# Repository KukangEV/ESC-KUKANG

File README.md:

## Why are We Building Electronic Speed Controller?

Creating an open source ESC can provide a significant contribution to the development of electric vehicles and EV technology in general. By making this technology openly available, developers and EV enthusiasts in Indonesia and around the world can easily access and modify the ESC.

In addition, by accelerating the development of EV, we can reduce our dependence on dwindling fossil fuels and produce fewer carbon emissions that harm the environment. Through open source ESC, we can encourage the development of more efficient and environmentally friendly technologies for future vehicles.

Moreover, this project can inspire young Indonesians to become more active in the automotive and EV technology industry. With an open source platform, we can develop creativity and innovative ideas that can help produce better technology and advance the automotive industry in Indonesia and around the world. Thus, this project will have a long-term positive impact on society and the environment.

## What is the ESC-KUKANG?

ESC (Electronic Speed Controller) is an important component in electric vehicles, including for the purposes of the Shell Eco-marathon. The ESC functions to control the current and voltage supplied to the DC motor in electric vehicles. The ESC usually uses a MOSFET as a switch which is regulated by a control circuit, and uses PWM (Pulse Width Modulation) to control the speed of the motor.

In the context of the Shell Eco-marathon, the ESC used must be designed in such a way that it is efficient in energy use, lightweight, and can produce power output as needed. This is very important because the vehicle must have enough endurance to cover the required distance with minimal battery usage.

To achieve this goal, several things that need to be considered in the ESC design for Shell Eco-marathon are the selection of components that are efficient and can work at high frequencies (around 16 kHz), the use of MOSFETs with low Rds-on values, the use of appropriate capacitors at input and output regulators to minimize noise and ripple, and the use of a PCB (Printed Circuit Board) with a good layout to minimize noise and EMI (Electromagnetic Interference). In addition, the ESC design must also consider safety factors and protection against overcurrent, overvoltage and overheating.

## How does it work?

ESC (Electronic Speed Controller) is an electronic circuit that functions to control the speed of an electric motor. When given a control signal from the remote or other controller, the ESC will convert the signal into a control signal to speed up or slow down the motor rotation.

ESC works by adjusting the amount of energy supplied to the motor. The ESC regulates the electric current that is supplied to the motor via a MOSFET or other power transistor. When the ESC receives a stronger control signal, the MOSFET opens wide and allows a greater amperage to flow to the motor, causing the motor to spin faster. Conversely, when the ESC receives a weaker control signal, the MOSFET will close more and limit the amperage flowing to the motor, causing the motor to rotate more slowly.

The ESC is also equipped with security protections such as protection from overcurrent, overheat and low voltage which will turn off the motor if there is a problem with the system.

## Installation
coming soon
## Contributors

## License

This project is licensed under the Apache 2 License - see the [LICENSE](LICENSE) file for details.

## Version

See `library.json` (PlatformIO) or `library.properties` (Arduino).

v0.0.1

[KUKANG-EV]: <https://kukang-ev.tech/>

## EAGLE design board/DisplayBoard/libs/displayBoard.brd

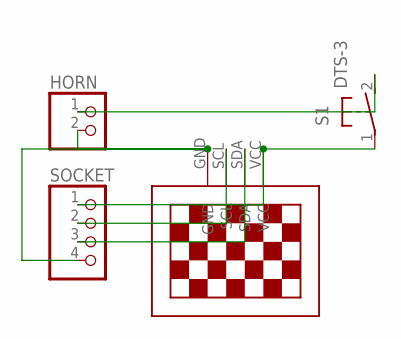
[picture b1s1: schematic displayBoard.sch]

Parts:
HORN: PINHD-1X2; 1X02
S1: DTS-3
SOCKET: PINHD-1X4; 1X04
U$1: 13"OLED13"OLED; 1.3"OLED

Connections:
unnamed: HORN.1, S1.2
unnamed: S1.1, SOCKET.1, U$1.VCC
unnamed: HORN.2, SOCKET.4, U$1.GND
unnamed: SOCKET.2, U$1.SCL
unnamed: SOCKET.3, U$1.SDA

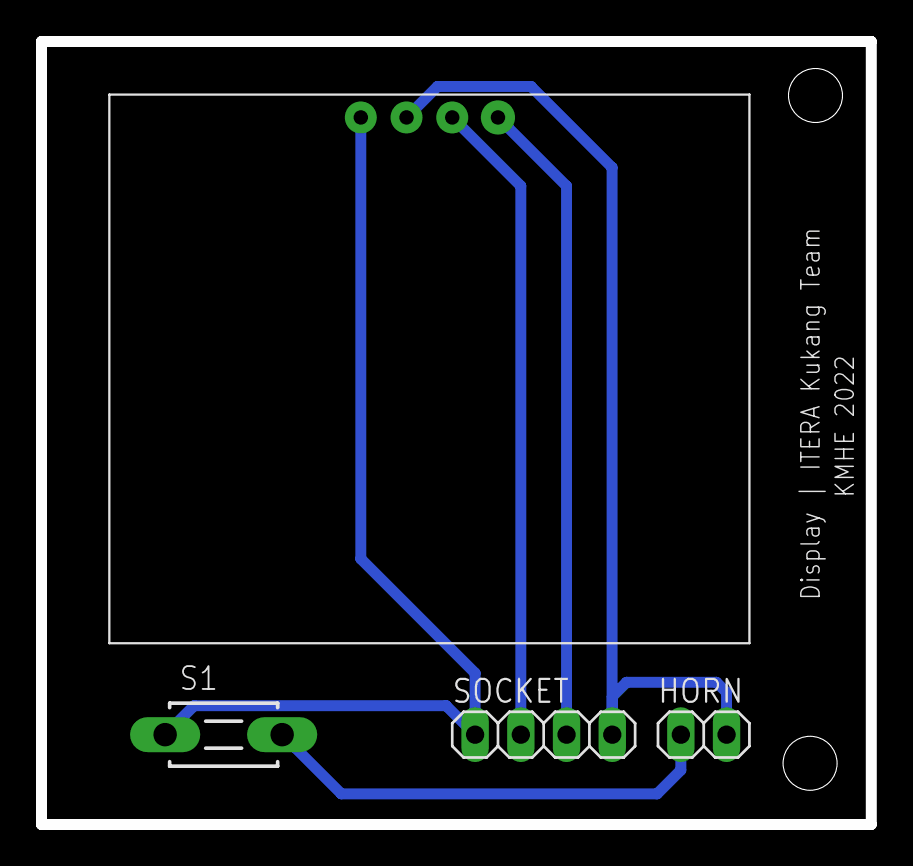
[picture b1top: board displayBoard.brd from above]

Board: 2 copper layers, 46.1 x 43.5 mm, 4 parts (0 on the bottom side), 5 nets.

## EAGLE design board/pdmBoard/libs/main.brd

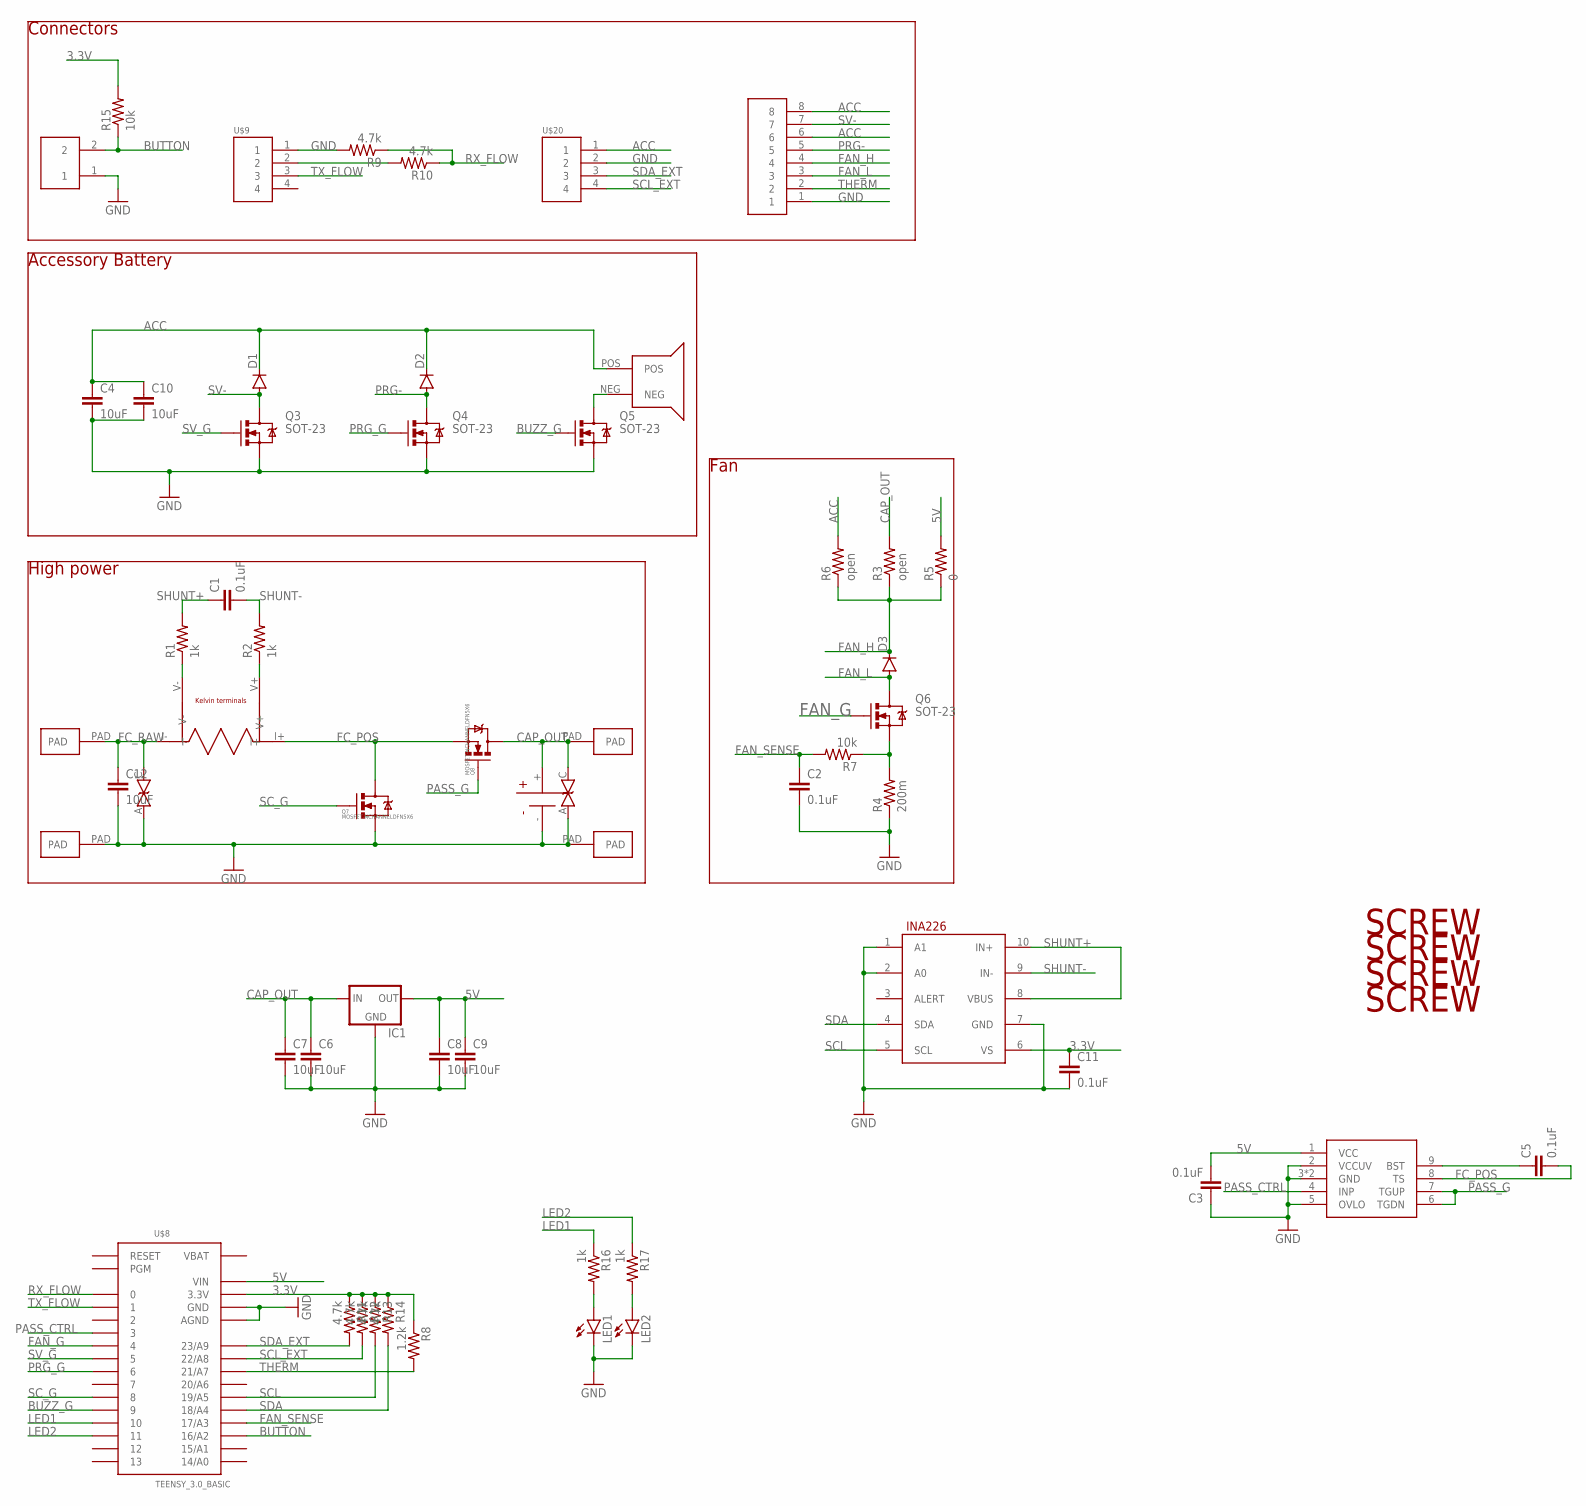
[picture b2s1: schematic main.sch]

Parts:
C1, C2, C3, C5, C11: 0.1uF; 0603-CAP
C4, C6, C7, C8, C9, C10, C12: 10uF; 1206
D1, D2, D3: DIODESOD123; SOD-123
IC1: V_REG_78XXV78W; V78W
LED1, LED2: LED1206; LED-1206
Q3, Q4, Q5, Q6: SOT-23; SOT23-3
Q7, Q8: MOSFET-NCHANNELDFN5X6; DFN5X6
R1, R2, R16, R17: 1k; 0603-RES
R3, R6: open; 0603-RES
R4: 200m; 0603-RES
R5: 0; 0603-RES
R7, R15: 10k; 0603-RES
R8: 1.2k; 0603-RES
R9, R10, R11, R12, R13, R14: 4.7k; 0603-RES
U$1: SHUNT_KELVIN; 2512_KELVIN
U$2: INA226; PSOP-10
U$3, U$4, U$10, U$11: PAD
U$5: HEADER8; 8PINVALULOK
U$6: LTC7001; PSOP-10-EP
U$7: BUZZER12MM; BUZZER_12MM
U$8: TEENSY_3.0_BASIC
U$9, U$20: HEADER4VALULOK; 4PINVALULOK
U$12: CAP-AL_ELECTROLYTIC; CAP-RADIAL
U$13: HEADER2; 2PINVALULOK
U$14, U$15, U$18, U$19: SCREW; M3HOLE
U$16, U$17: TVS_BIDO-214AB; DO-214AB

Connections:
3.3V: C11.1, R8.1, R11.1, R12.1, R13.1, R14.1, R15.2, U$2.6 (VS), U$8.3.3V, U$8.3.3V1 (3.3V)
5V: C3.2, C8.1, C9.1, IC1.OUT, R5.2, U$6.1 (VCC), U$8.VIN
ACC: C4.1, C10.1, D1.C, D2.C, R6.2, U$5.6, U$5.8, U$7.POS, U$20.1
BUTTON: R15.1, U$8.16/A2, U$13.2
BUZZ_G: Q5.1 (G), U$8.9
CAP_OUT: C6.1, C7.1, IC1.IN, Q8.PAD (D), R3.2, U$10.PAD, U$12.+ (V+), U$17.C (2)
FAN_G: Q6.1 (G), U$8.4
FAN_H: D3.C, R3.1, R5.1, R6.1, U$5.4
FAN_L: D3.A, Q6.3 (D), U$5.3
FAN_SENSE: C2.1, R7.2, U$8.17/A3
FC_POS: C5.2, Q7.PAD (D), Q8.1 (S), Q8.2 (S), Q8.3 (S), U$1.I+, U$6.8 (TS)
FC_RAW: C12.1, U$1.I-, U$3.PAD, U$16.C (2)
GND: C2.2, C3.1, C4.2, C6.2, C7.2, C8.2, C9.2, C10.2, C11.2, C12.2, IC1.GND, LED1.C, LED2.C, Q3.2 (S), Q4.2 (S), Q5.2 (S), Q7.1 (S), Q7.2 (S), Q7.3 (S), R4.1, R9.2, U$2.1 (A1), U$2.2 (A0), U$2.7 (GND), U$4.PAD, U$5.1, U$6.2 (VCCUV), U$6.3 (GND), U$6.5 (OVLO), U$6.PAD (GND), U$8.AGND, U$8.GND, U$8.GND1 (GND), U$9.1, U$11.PAD, U$12.- (V-), U$13.1, U$16.A (1), U$17.A (1), U$20.2
LED1: R16.1, U$8.10
LED2: R17.1, U$8.11
unnamed: C5.1, U$6.9 (BST)
unnamed: LED1.A, R16.2
unnamed: Q5.3 (D), U$7.NEG
unnamed: R1.1, U$1.V-
unnamed: R2.1, U$1.V+
unnamed: Q6.2 (S), R4.2, R7.1
unnamed: R10.2, U$9.2
unnamed: LED2.A, R17.2
PASS_CTRL: U$6.4 (INP), U$8.3
PASS_G: Q8.4 (G), U$6.6 (TGDN), U$6.7 (TGUP)
PRG-: D2.A, Q4.3 (D), U$5.5
PRG_G: Q4.1 (G), U$8.6
RX_FLOW: R9.1, R10.1, U$8.0
SCL: R13.2, U$2.5 (SCL), U$8.19/A5
SCL_EXT: R12.2, U$8.22/A8, U$20.4
SC_G: Q7.4 (G), U$8.8
SDA: R14.2, U$2.4 (SDA), U$8.18/A4
SDA_EXT: R11.2, U$8.23/A9, U$20.3
SHUNT+: C1.1, R1.2, U$2.8 (VBUS), U$2.10 (IN+)
SHUNT-: C1.2, R2.2, U$2.9 (IN-)
SV-: D1.A, Q3.3 (D), U$5.7
SV_G: Q3.1 (G), U$8.5
THERM: R8.2, U$5.2, U$8.21/A7
TX_FLOW: U$8.1, U$9.3
VBAT: U$8.VBAT

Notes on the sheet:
Accessory Battery
High power
Fan
Connectors

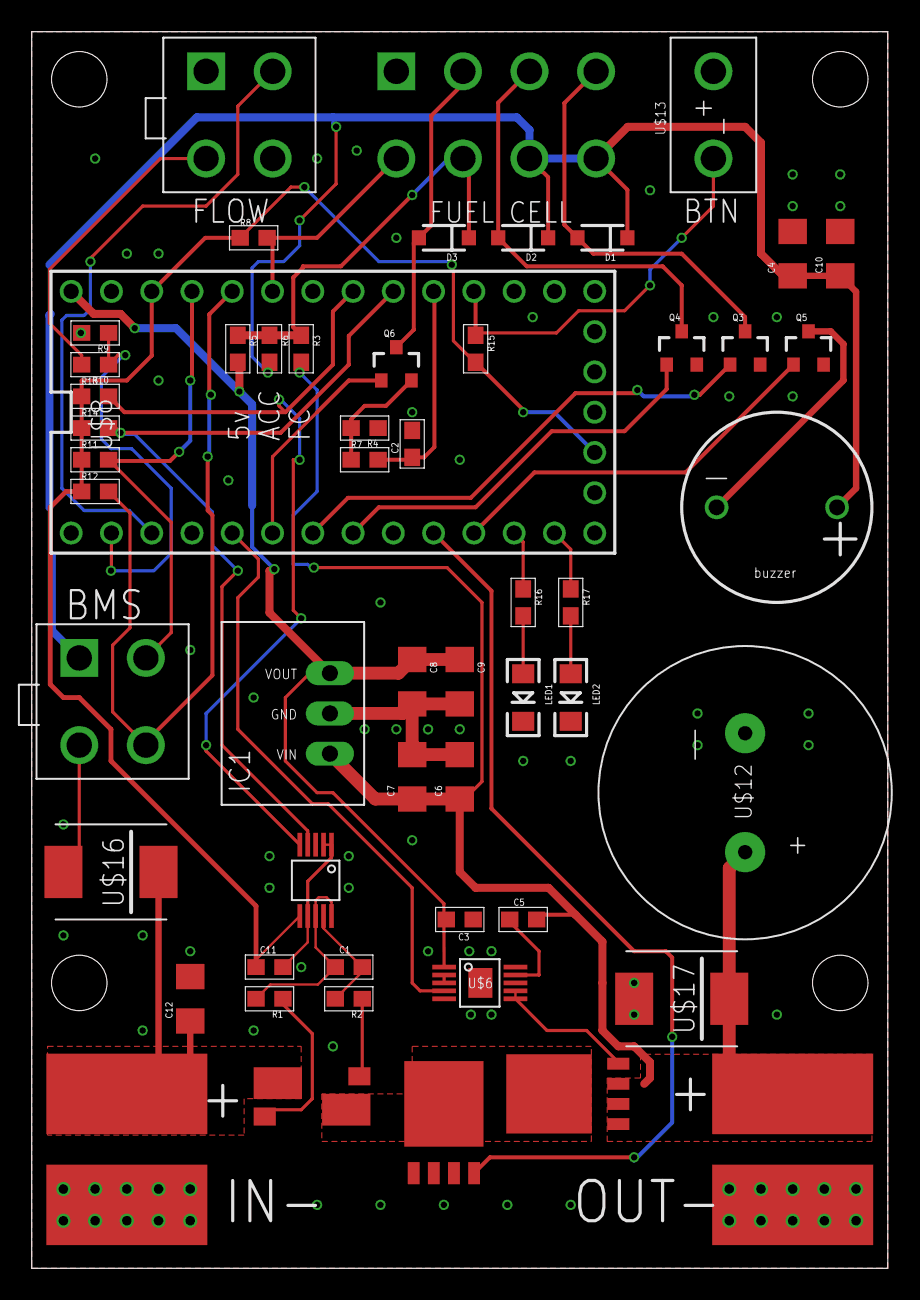
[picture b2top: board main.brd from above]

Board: 2 copper layers, 54.0 x 78.0 mm, 61 parts (0 on the bottom side), 39 nets.

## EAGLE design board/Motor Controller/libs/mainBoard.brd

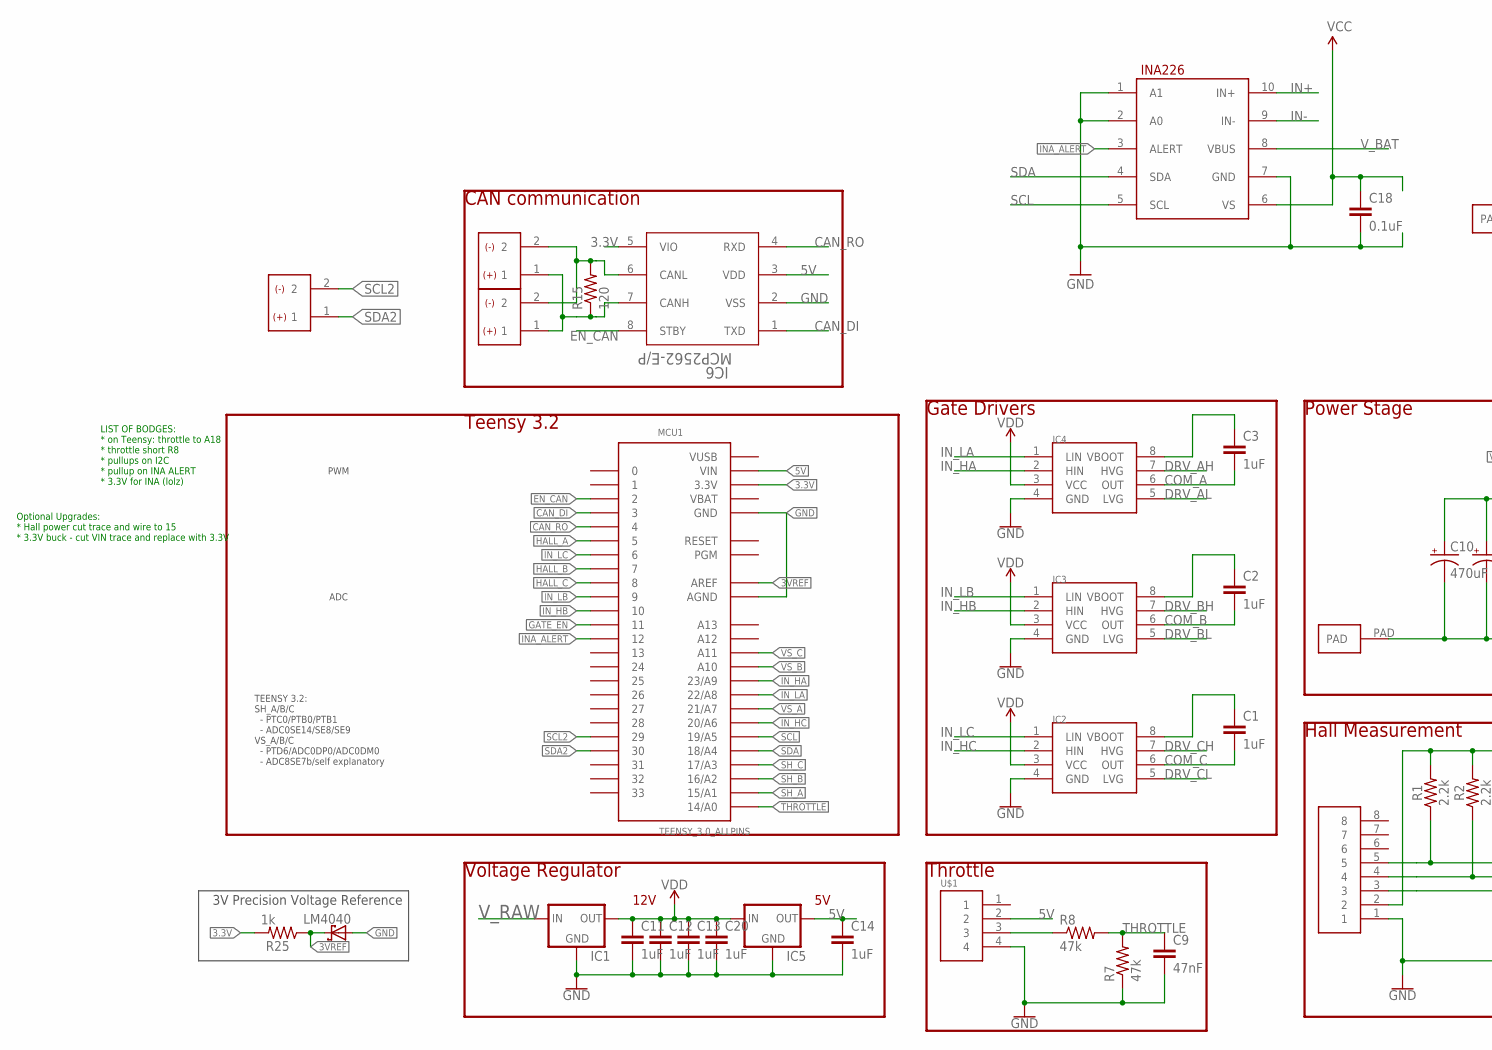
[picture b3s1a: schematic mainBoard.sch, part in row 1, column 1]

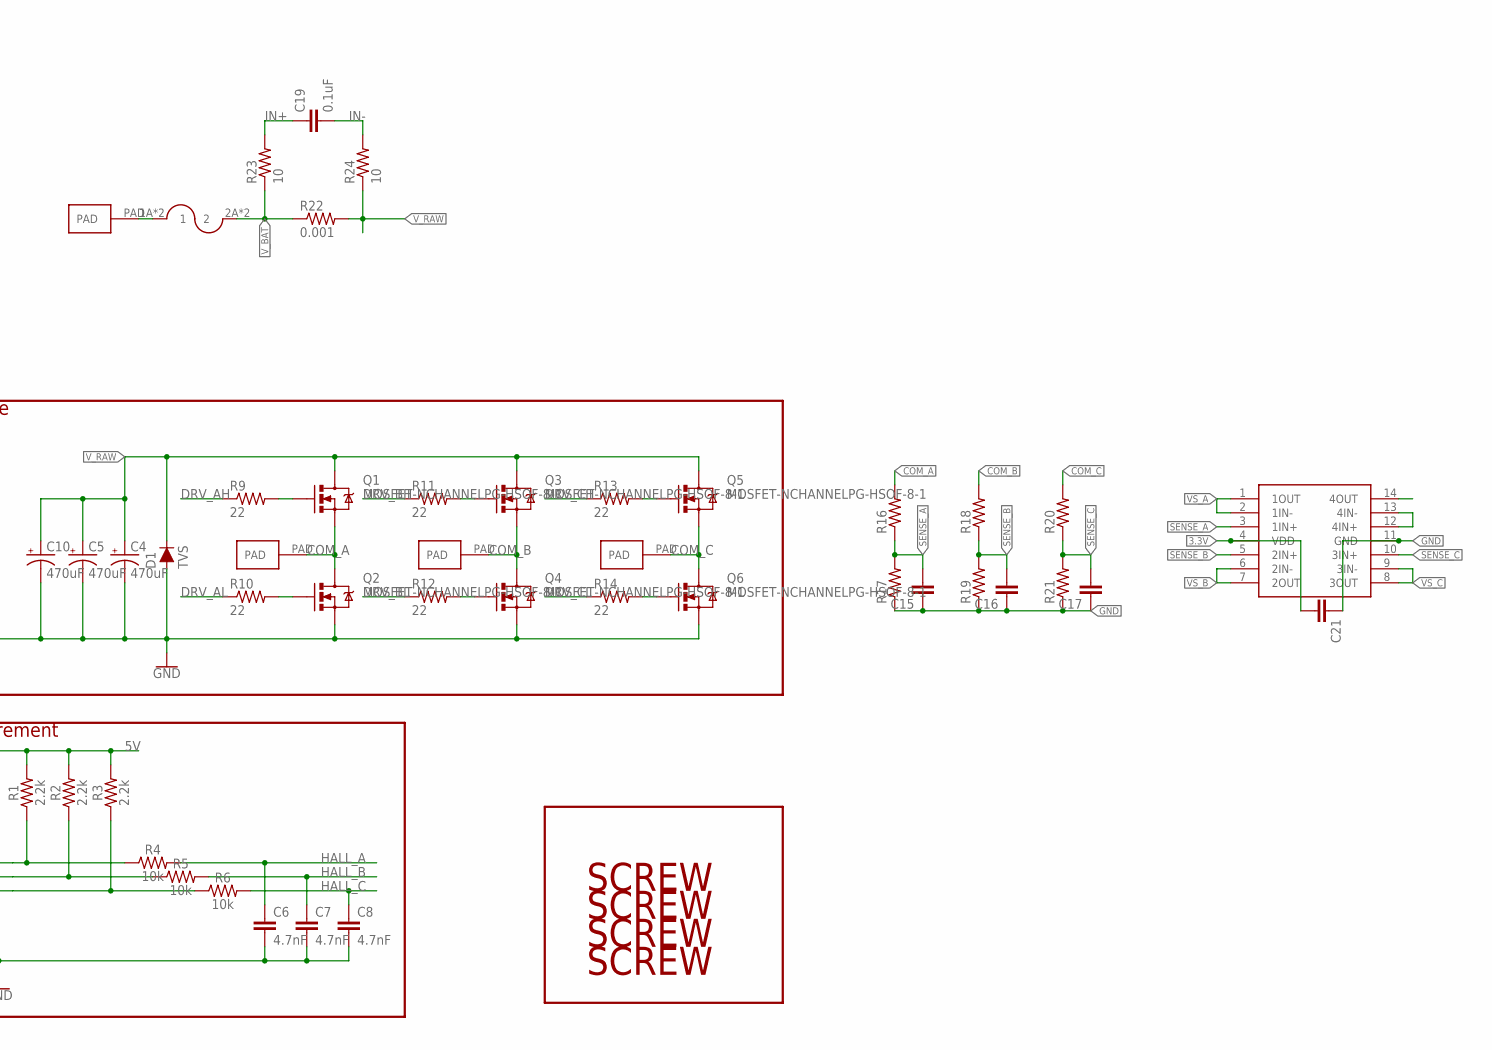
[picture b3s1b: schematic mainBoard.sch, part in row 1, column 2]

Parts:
C1, C2, C3, C11, C12, C13, C14, C20: 1uF; CAP-PTH-SMALL-KIT
C4, C5, C10: 470uF; CPOL-RADIAL-5MM-10MM
C6, C7, C8: 4.7nF; 0603-CAP
C9: 47nF; 0603-CAP
C15, C16, C17, C21: CAP0603-CAP; 0603-CAP
C18, C19: 0.1uF; 0603-CAP
CAN1, CAN2: HEADER2; 2PINVALULOK
D1: TVS; DIODE-1N4001
I2C: HEADER2; 2PINVALULOK
IC1: V_REG_78XX; V78W_BACKWARDS
IC2, IC3, IC4: L6387EDIP8; DIP762W53P254L1092H508Q8B
IC5: V_REG_78XXV78W; V78W
IC6: MCP2562-E/P; PDIP8_300MC
IC7: INA226; PSOP-10
J3: FUSE; AUTO_FUSE
MCU1: TEENSY_3.0_ALLPINS
Q1, Q2, Q3, Q4, Q5, Q6: MOSFET-NCHANNELPG-HSOF-8-1; PG-HSOF-8-1
R1, R2, R3: 2.2k; 0603-RES
R4, R5, R6: 10k; 0603-RES
R7, R8: 47k; 0603-RES
R9, R10, R11, R12, R13, R14: 22; 0603-RES
R15: 120; 0603-RES
R16, R17, R18, R19, R20, R21: RESISTOR0603-RES; 0603-RES
R22: 0.001; R2512
R23, R24: 10; 0603-RES
R25: 1k; 0603-RES
U$1: HEADER4VALULOK; 4PINVALULOK
U$2: OPAMP_QUAD; TSSOP-14
U$4, U$5, U$6, U$7, U$8: PAD
U$10, U$11, U$12, U$13: SCREW; M3HOLE
U$14: HEADER8; 8PINVALULOK
U$15: LM4040; SOT23-3

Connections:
3.3V: C21.2, IC6.5 (VIO), MCU1.3.3V, MCU1.3.3V1 (3.3V), MCU1.3.3V2 (3.3V), R25.2, U$2.4 (VDD)
3VREF: MCU1.AREF, R25.1, U$15.1 (C)
5V: C14.1, IC5.OUT, IC6.3 (VDD), MCU1.VIN, R1.2, R2.2, R3.2, U$1.2, U$14.2
CANH: CAN1.1, CAN2.1, IC6.7 (CANH), R15.1
CANL: CAN1.2, CAN2.2, IC6.6 (CANL), R15.2
CAN_DI: IC6.1 (TXD), MCU1.3
CAN_RO: IC6.4 (RXD), MCU1.4
COM_A: C3.2, IC4.6 (OUT), Q1.S, Q2.D, R16.2, U$6.PAD
COM_B: C2.2, IC3.6 (OUT), Q3.S, Q4.D, R18.2, U$7.PAD
COM_C: C1.2, IC2.6 (OUT), Q5.S, Q6.D, R20.2, U$8.PAD
DRV_AH: IC4.7 (HVG), R9.1
DRV_AL: IC4.5 (LVG), R10.1
DRV_BH: IC3.7 (HVG), R11.1
DRV_BL: IC3.5 (LVG), R12.1
DRV_CH: IC2.7 (HVG), R13.1
DRV_CL: IC2.5 (LVG), R14.1
EN_CAN: IC6.8 (STBY), MCU1.2
GATE_EN: MCU1.11
GND: C4.-, C5.-, C6.2, C7.2, C8.2, C9.2, C10.-, C11.2, C12.2, C13.2, C14.2, C15.1, C16.1, C17.1, C18.2, C20.2, C21.1, D1.A, IC1.GND, IC2.4 (GND), IC3.4 (GND), IC4.4 (GND), IC5.GND, IC6.2 (VSS), IC7.1 (A1), IC7.2 (A0), IC7.7 (GND), MCU1.AGND, MCU1.GND, MCU1.GND1 (GND), MCU1.GND2 (GND), Q2.S, Q4.S, Q6.S, R7.1, R17.1, R19.1, R21.1, U$1.4, U$2.11 (GND), U$5.PAD, U$14.1, U$15.2 (A)
HALL_A: C6.1, MCU1.5, R4.2
HALL_B: C7.1, MCU1.7, R5.2
HALL_C: C8.1, MCU1.8, R6.2
IN+: C19.1, IC7.10 (IN+), R23.2
IN-: C19.2, IC7.9 (IN-), R24.2
INA_ALERT: IC7.3 (ALERT), MCU1.12
IN_HA: IC4.2 (HIN), MCU1.23/A9
IN_HB: IC3.2 (HIN), MCU1.10
IN_HC: IC2.2 (HIN), MCU1.20/A6
IN_LA: IC4.1 (LIN), MCU1.22/A8
IN_LB: IC3.1 (LIN), MCU1.9
IN_LC: IC2.1 (LIN), MCU1.6
unnamed: C1.1, IC2.8 (VBOOT)
unnamed: R3.1, R6.1, U$14.3
unnamed: C2.1, IC3.8 (VBOOT)
unnamed: R2.1, R5.1, U$14.4
unnamed: C3.1, IC4.8 (VBOOT)
unnamed: R1.1, R4.1, U$14.5
unnamed: R8.1, U$1.3
unnamed: Q1.G, R9.2
unnamed: Q2.G, R10.2
unnamed: Q3.G, R11.2
unnamed: Q4.G, R12.2
unnamed: Q5.G, R13.2
unnamed: Q6.G, R14.2
unnamed: U$2.12 (4IN+), U$2.13 (4IN-)
SCL: IC7.5 (SCL), MCU1.19/A5
SCL2: I2C.2, MCU1.29
SDA: IC7.4 (SDA), MCU1.18/A4
SDA2: I2C.1, MCU1.30
SENSE_A: C15.2, R16.1, R17.2, U$2.3 (1IN+)
SENSE_B: C16.2, R18.1, R19.2, U$2.5 (2IN+)
SENSE_C: C17.2, R20.1, R21.2, U$2.10 (3IN+)
SH_A: MCU1.15/A1
SH_B: MCU1.16/A2
SH_C: MCU1.17/A3
THROTTLE: C9.1, MCU1.14/A0, R7.2, R8.2
VBAT: MCU1.VBAT
VCC: C18.1, IC7.6 (VS)
VDD: C11.1, C12.1, C13.1, C20.1, IC1.OUT, IC2.3 (VCC), IC3.3 (VCC), IC4.3 (VCC), IC5.IN
VS_A: MCU1.21/A7, U$2.1 (1OUT), U$2.2 (1IN-)
VS_B: MCU1.A10, U$2.6 (2IN-), U$2.7 (2OUT)
VS_C: MCU1.A11, U$2.8 (3OUT), U$2.9 (3IN-)
VUSB: MCU1.VUSB
V_BAT: IC7.8 (VBUS), J3.2A (2), J3.2B (2), R22.1, R23.1
V_PREFUSE: J3.1A (1), J3.1B (1), U$4.PAD
V_RAW: C4.+, C5.+, C10.+, D1.C, IC1.IN, Q1.D, Q3.D, Q5.D, R22.2, R24.1

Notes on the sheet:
Power Stage
Hall Measurement
Gate Drivers
Throttle
Teensy 3.2
Voltage Regulator
12V
CAN communication
PWM
ADC
TEENSY 3.2: SH_A/B/C - PTC0/PTB0/PTB1 - ADC0SE14/SE8/SE9 VS_A/B/C - PTD6/ADC0DP0/ADC0DM0 - ADC8SE7b/self explanatory
3V Precision Voltage Reference
LIST OF BODGES: * on Teensy: throttle to A18 * throttle short R8 * pullups on I2C * pullup on INA ALERT * 3.3V for INA (lolz)
Optional Upgrades: * Hall power cut trace and wire to 15 * 3.3V buck - cut VIN trace and replace with 3.3V

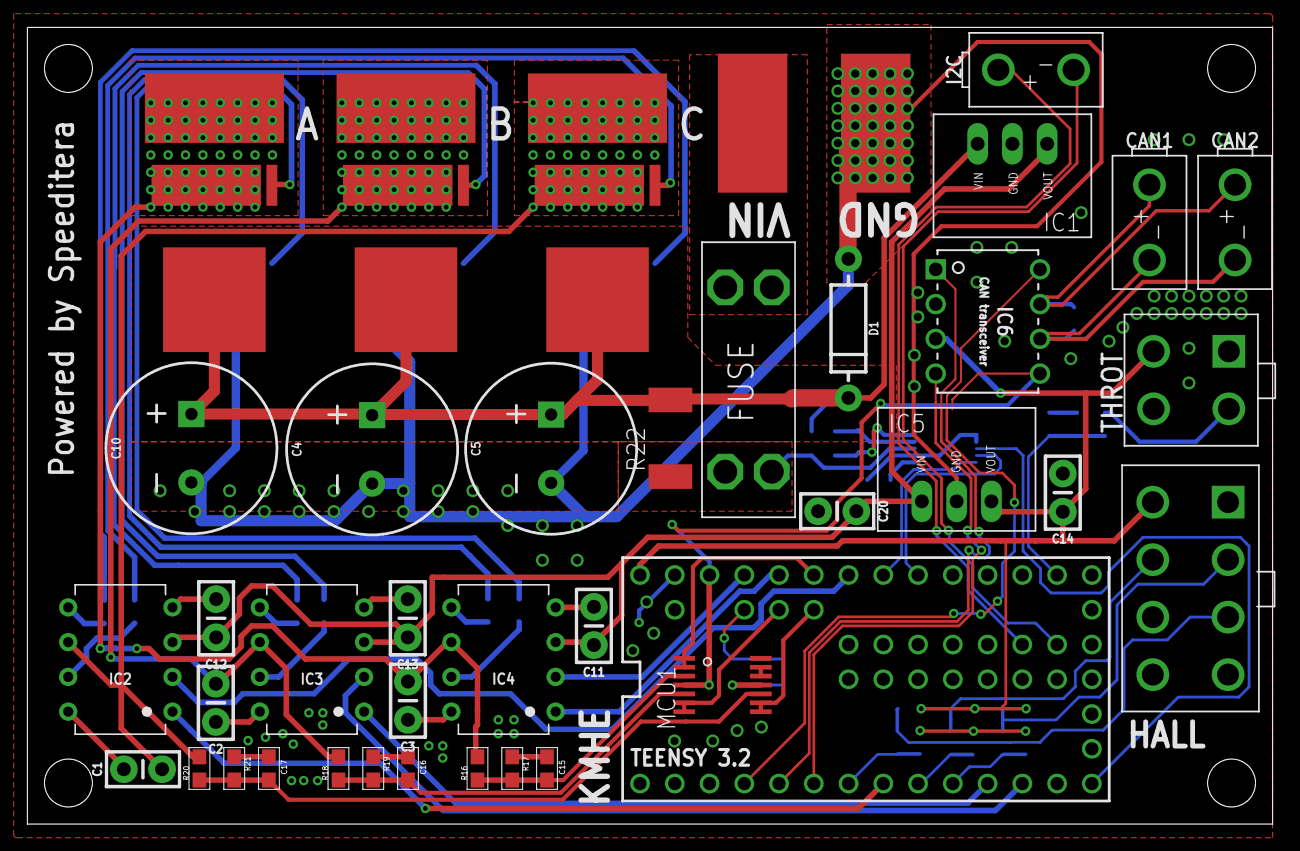
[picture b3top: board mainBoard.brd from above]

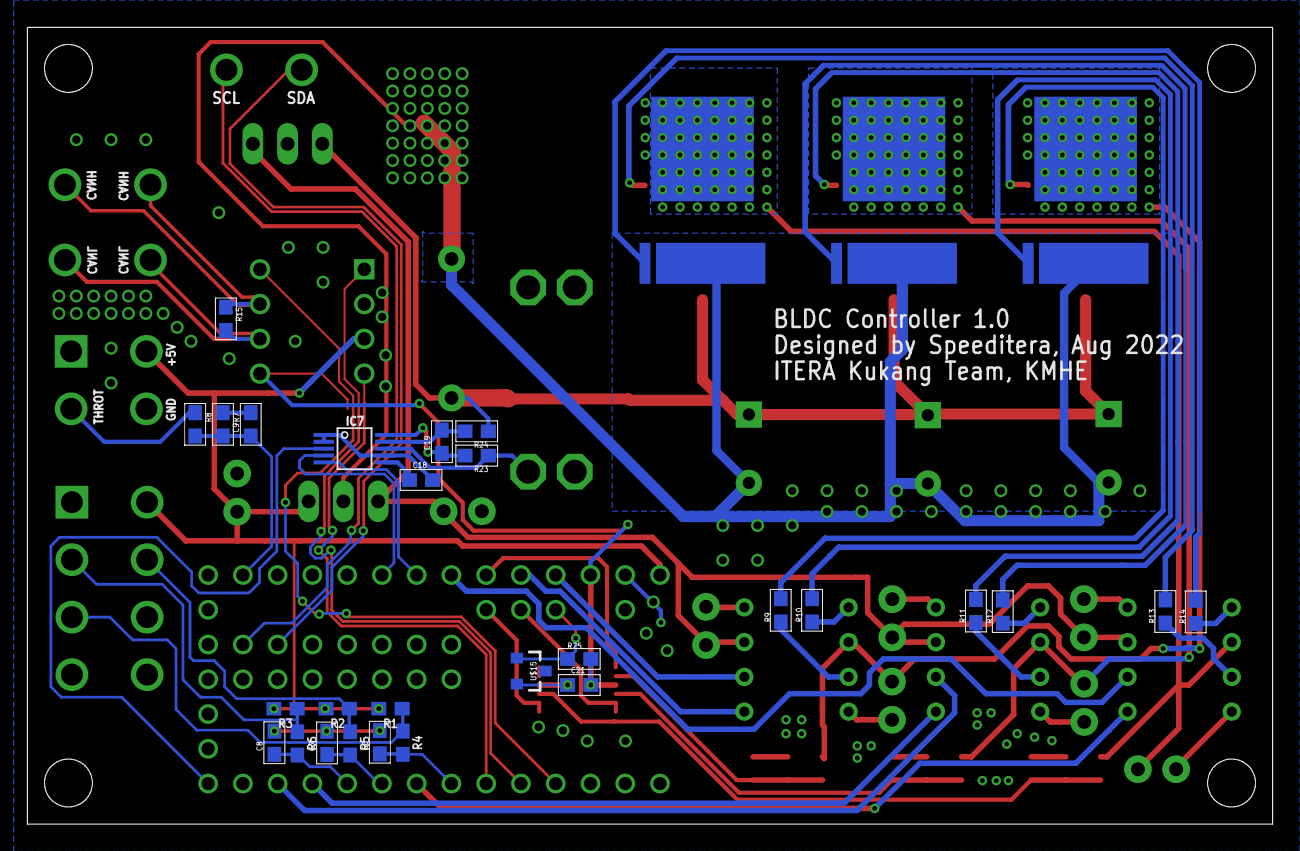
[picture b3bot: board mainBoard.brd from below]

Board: 2 copper layers, 91.0 x 58.2 mm, 79 parts (31 on the bottom side), 60 nets.

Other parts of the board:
U$3: DEV

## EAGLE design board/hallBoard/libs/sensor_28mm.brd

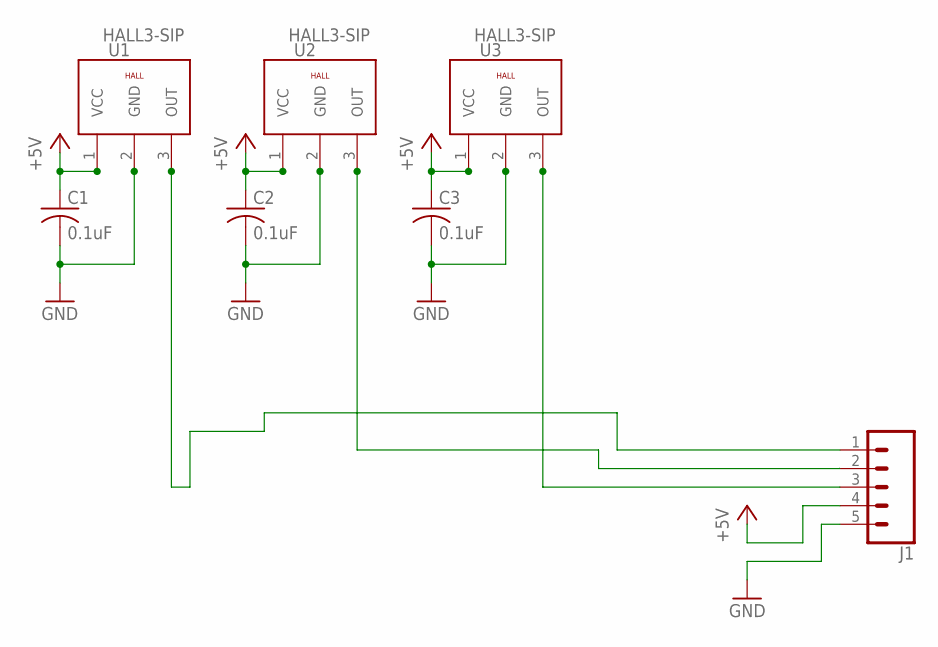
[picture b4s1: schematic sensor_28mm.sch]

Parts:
C1, C2, C3: 0.1uF; C0603
J1: CONN_05PTH_LONGPADS; 1X05_LONGPADS
U1, U2, U3: HALL3-SIP; 3PINS1,27

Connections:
+5V: C1.1, C2.1, C3.1, J1.4, U1.1 (VCC), U2.1 (VCC), U3.1 (VCC)
GND: C1.2, C2.2, C3.2, J1.5, U1.2 (GND), U2.2 (GND), U3.2 (GND)
unnamed: J1.1, U1.3 (OUT)
unnamed: J1.3, U3.3 (OUT)
unnamed: J1.2, U2.3 (OUT)

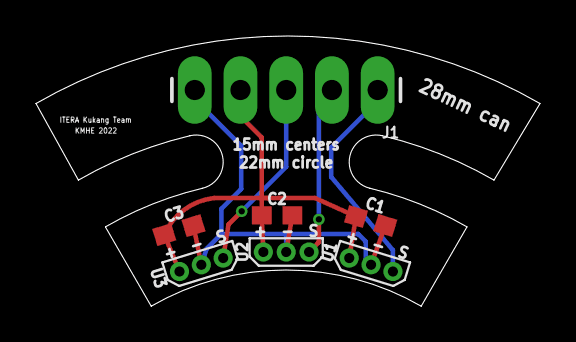
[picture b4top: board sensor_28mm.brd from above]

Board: 2 copper layers, 28.0 x 15.0 mm, 7 parts (0 on the bottom side), 5 nets.

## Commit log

2022-08-20 assets pcb viewer
2022-08-20 sch & brd all item
2022-08-20 sample code
2022-08-20 documentation
2022-08-21 update Documentation
2022-08-21 add flow wired & board
2022-08-21 improve new board
2022-08-21 update fix bugs
2022-08-21 fix bugs
2023-02-21 new setup and docs

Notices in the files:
README.md:
License: Apache2
parts and their libraries:
SparkFun-Capacitors: Licensing: Creative Commons ShareAlike 4.0 International - https://creativecommons.org/licenses/by-sa/4.0
